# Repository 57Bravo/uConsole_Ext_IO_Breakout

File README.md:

# uConsole External I/O Breakout - REV: A

## BEWARE!!! --- THIS DESIGN HAS NOT BEEN VERIFIED --- BEWARE!!!

This is a generic breakout board for ClockWorkPI's uConsole. I didn't order the cellular module, and wanted to use the external I/O slot. Here's the "REV: A" SWAG based off of renderings of the PCB.

I have not verified this design. Once I get the boards back from OshPark, stuffed, and tested on the uConsole; I'll tag a release. 

**Also, I don't work for CPI, and this is not an official board from them. I just threw their logo on there, since the uConsole is their gear. Show CPI some love, and checkout their products! :)**

https://www.clockworkpi.com/

https://github.com/clockworkpi/uConsole/blob/master/clockwork_Adapter_CM4_Schematic.pdf

https://github.com/clockworkpi/DevTerm/tree/main/Schematics

## REV: A

**Epic fail on REV: A.**

When I made it, CPI hadn't released the DXF for the 4G card yet. I had to eyeball the board outline based on the website images. I missed the outer edge by 1mm. 

Luckily the edge was just ground plane, and I was able to file the FR4 back to get it to fit. Continuity checks out, but.... I think a REV: B is in order ha.

The fixes for REV: B are:
* fix the board outline to account for the thicker enclosure wall
* refactor the audio so that the onboard speakers can be used instead of the JSTs
* flip the QWIIC connectors so they don't interfere with the speaker housings
* pull the USB connectors in a little so they're flush with the enclosure wall

## Notes

### Other boards made by Quadbit (Vitaly Domnikov), that you can buy on Tindie

* [uPico](https://www.tindie.com/products/quadbit/upico/)
  * [Src](https://github.com/dotcypress/upico)
* [uHub](https://www.tindie.com/products/quadbit/uhub/)
  * [Src](https://github.com/dotcypress/uhub)

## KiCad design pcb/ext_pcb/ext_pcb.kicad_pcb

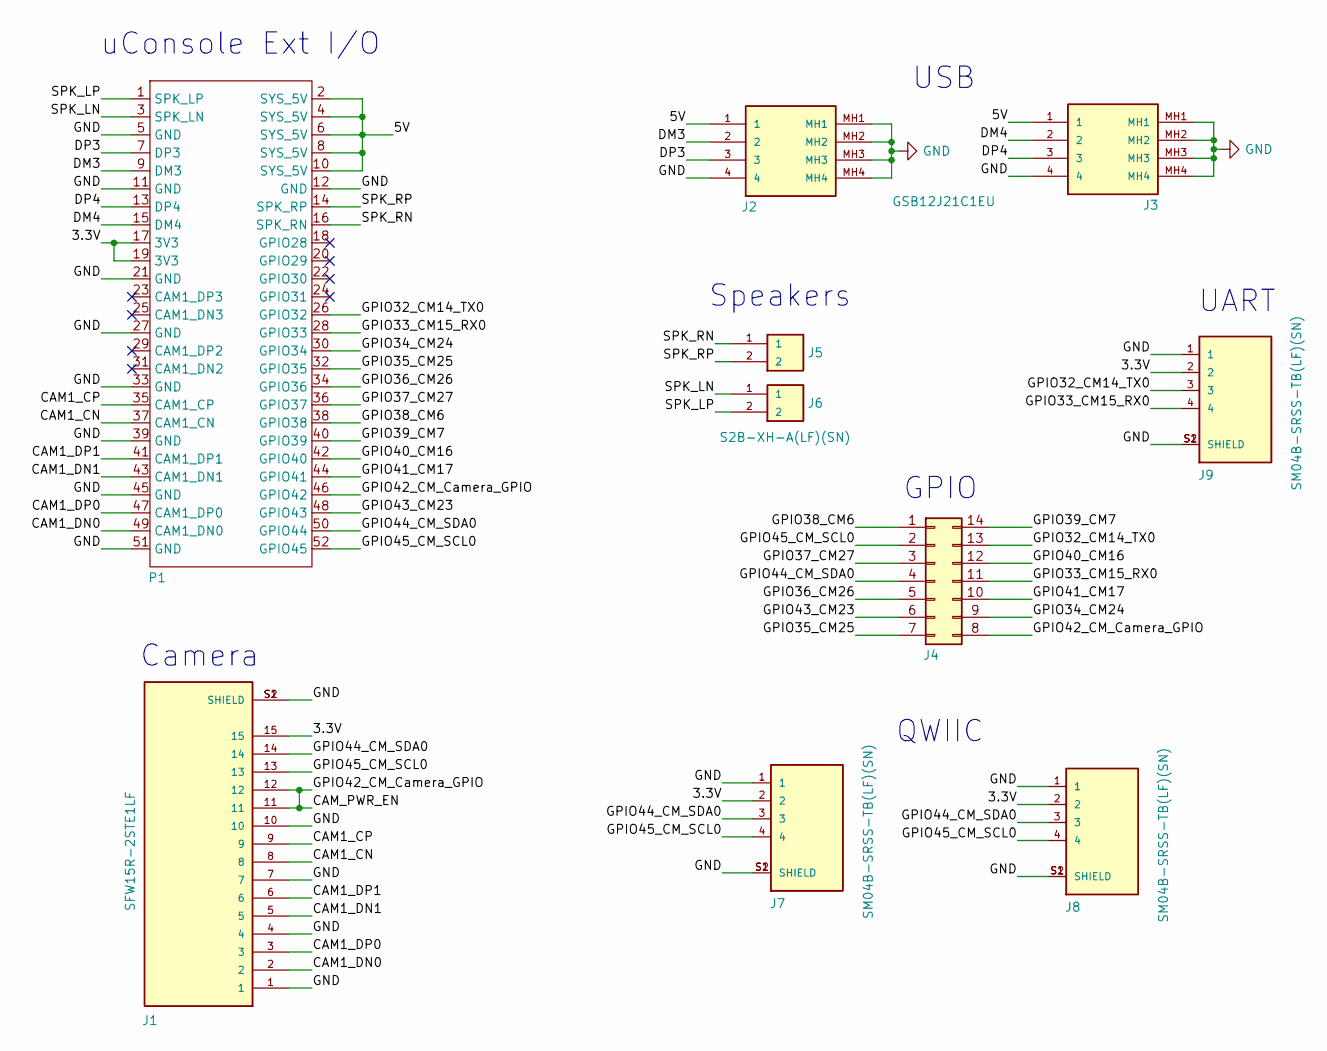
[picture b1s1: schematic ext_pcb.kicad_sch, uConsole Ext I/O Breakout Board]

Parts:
J1: SFW15R-2STE1LF; AMPHENOL_SFW15R-2STE1LF; PARTREV AE
J2, J3: GSB12J21C1EU; MOUSER_PART_NUMBER 523-GSB12J21C1EU
J4: Conn_02x07_Counter_Clockwise; PinHeader_2x07_P2.54mm_Vertical
J5, J6: S2B-XH-A(LF)(SN); JST_S2B-XH-A(LF)(SN)
J7, J8, J9: SM04B-SRSS-TB(LF)(SN); JST_SM04B-SRSS-TB(LF)(SN)
P1: ext_card_fp

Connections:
/3.3V: J1.15, J7.2, J8.2, J9.2, P1.17 (3V3), P1.19 (3V3)
/5V: J2.1, J3.1, P1.2 (SYS_5V), P1.4 (SYS_5V), P1.6 (SYS_5V), P1.8 (SYS_5V), P1.10 (SYS_5V)
/CAM1_CN: J1.8, P1.37 (CAM1_CN)
/CAM1_CP: J1.9, P1.35 (CAM1_CP)
/CAM1_DN0: J1.2, P1.49 (CAM1_DN0)
/CAM1_DN1: J1.5, P1.43 (CAM1_DN1)
/CAM1_DP0: J1.3, P1.47 (CAM1_DP0)
/CAM1_DP1: J1.6, P1.41 (CAM1_DP1)
/CAM_PWR_EN: J1.11, J1.12, J4.8, P1.46 (GPIO42)
/DM3: J2.2, P1.9 (DM3)
/DM4: J3.2, P1.15 (DM4)
/DP3: J2.3, P1.7 (DP3)
/DP4: J3.3, P1.13 (DP4)
/GPIO32_CM14_TX0: J4.13, J9.3, P1.26 (GPIO32)
/GPIO33_CM15_RX0: J4.11, J9.4, P1.28 (GPIO33)
/GPIO34_CM24: J4.9, P1.30 (GPIO34)
/GPIO35_CM25: J4.7, P1.32 (GPIO35)
/GPIO36_CM26: J4.5, P1.34 (GPIO36)
/GPIO37_CM27: J4.3, P1.36 (GPIO37)
/GPIO38_CM6: J4.1, P1.38 (GPIO38)
/GPIO39_CM7: J4.14, P1.40 (GPIO39)
/GPIO40_CM16: J4.12, P1.42 (GPIO40)
/GPIO41_CM17: J4.10, P1.44 (GPIO41)
/GPIO43_CM23: J4.6, P1.48 (GPIO43)
/GPIO44_CM_SDA0: J1.14, J4.4, J7.3, J8.3, P1.50 (GPIO44)
/GPIO45_CM_SCL0: J1.13, J4.2, J7.4, J8.4, P1.52 (GPIO45)
/SPK_LN: J6.1, P1.3 (SPK_LN)
/SPK_LP: J6.2, P1.1 (SPK_LP)
/SPK_RN: J5.1, P1.16 (SPK_RN)
/SPK_RP: J5.2, P1.14 (SPK_RP)
GND: J1.1, J1.4, J1.7, J1.10, J1.S1 (SHIELD), J1.S2 (SHIELD), J2.4, J2.MH1, J2.MH2, J2.MH3, J2.MH4, J3.4, J3.MH1, J3.MH2, J3.MH3, J3.MH4, J7.1, J7.S1 (SHIELD), J7.S2 (SHIELD), J8.1, J8.S1 (SHIELD), J8.S2 (SHIELD), J9.1, J9.S1 (SHIELD), J9.S2 (SHIELD), P1.5 (GND), P1.11 (GND), P1.12 (GND), P1.21 (GND), P1.27 (GND), P1.33 (GND), P1.39 (GND), P1.45 (GND), P1.51 (GND)

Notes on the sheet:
GPIO
QWIIC
Camera
USB
uConsole Ext I/O
Speakers
UART

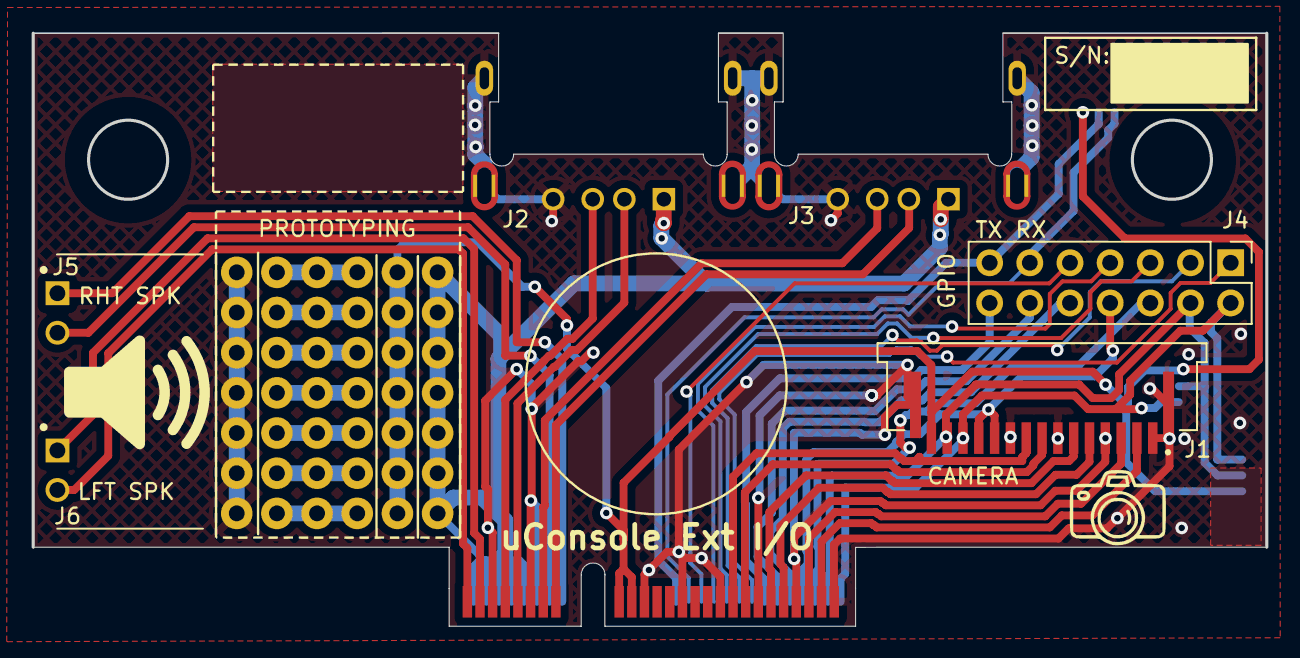
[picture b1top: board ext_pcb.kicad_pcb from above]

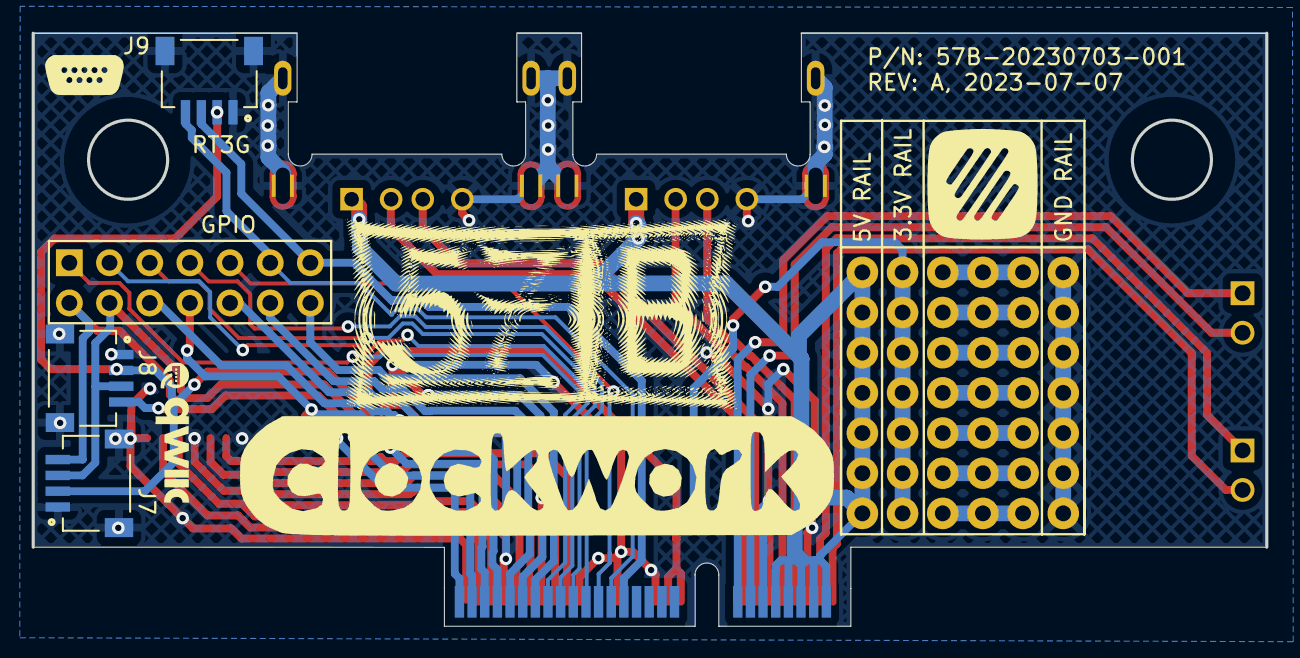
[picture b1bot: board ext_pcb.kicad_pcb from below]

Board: 2 copper layers, 78.0 x 37.4 mm, 10 parts (5 on the bottom side), 31 nets.

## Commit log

2023-07-04 export to GitHub
2023-07-09 REV: -
2023-07-09 REV: A
2023-07-25 added photo of populated board
2023-11-23 added notes on the 'REV: -' findings
2023-11-23 'REV: A' was sent to fab, not 'REV: -'
2023-11-24 added notes on other expansion boards
